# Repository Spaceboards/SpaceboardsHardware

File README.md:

# Spaceboards Hardware

### Status Key

❌  Unfinished

⚠️ Untested

✔️ Tested and functional 

### Designs
| Name     | Status | Contributors | 
|----------|--------|--------------|
|  2% Milk |  ✔️    | [PyroL](https://github.com/PyrooL), [Soft_Sama](https://www.thingiverse.com/soft_sama) |
|  Akimbo  |   ⚠️   |              |
|  LongBoi |   ❌   |              |
|Pancake v1|  ✔️  | [MKUltra Corp](https://kbd.news/vendors/MKUltra-129.html)  | 
|Pancake v2|  ✔️  | [MKUltra Corp](https://kbd.news/vendors/MKUltra-129.html)  |
|  Waffle  |  ⚠️    |              |
|  XLant   |  ⚠️    |              |

All of these files are shared under `CERN Open Hardware Licence Version 2 - Weakly Reciprocal`
Link this repository if you are selling any of these designs, These files are shared as is without any implied warranty or promise of being functional.

Visit our website at [https://spaceboards.github.io/](https://spaceboards.github.io/)

## Star History

<a href="https://www.star-history.com/?repos=Spaceboards%2FSpaceboardsHardware&type=date&legend=top-left">
 <picture>
   <source media="(prefers-color-scheme: dark)" srcset="https://api.star-history.com/chart?repos=Spaceboards/SpaceboardsHardware&type=date&theme=dark&legend=top-left" />
   <source media="(prefers-color-scheme: light)" srcset="https://api.star-history.com/chart?repos=Spaceboards/SpaceboardsHardware&type=date&legend=top-left" />
   
 </picture>
</a>

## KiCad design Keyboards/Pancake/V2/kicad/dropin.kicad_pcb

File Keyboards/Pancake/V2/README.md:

# Pancake v2

4x12 Choc v1 Ortho ultra low profile keyboard

- OLED screen

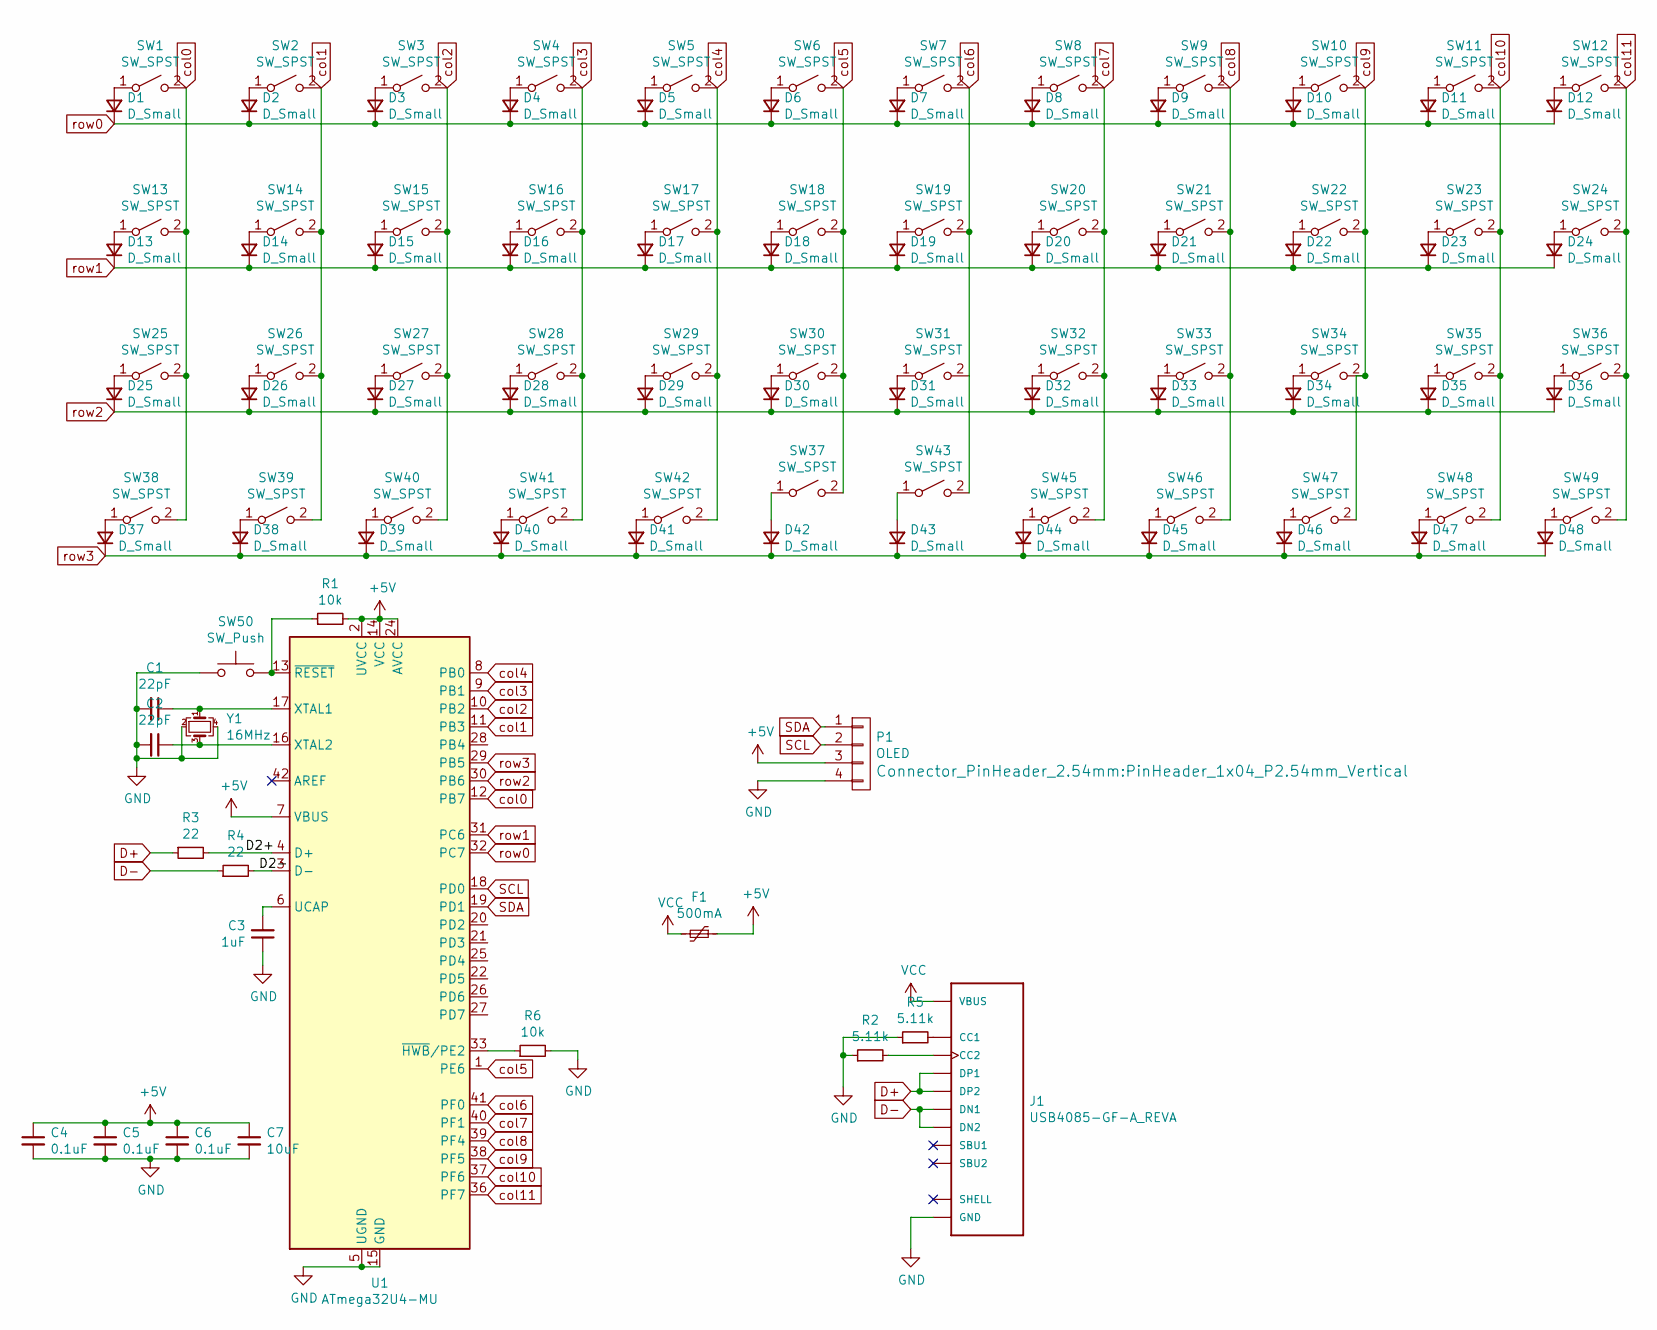
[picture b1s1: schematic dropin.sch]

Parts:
C1, C2: 22pF; C_0805_2012Metric
C3: 1uF; C_0805_2012Metric
C4, C5, C6: 0.1uF; C_0805_2012Metric
C7: 10uF; C_0805_2012Metric
D1, D2, D3, D4, D5, D6, D7, D8, D9, D10, D11, D12, D13, D14, D15, D16, D17, D18, D19, D20, D21, D22, D23, D24, D25, D26, D27, D28, D29, D30, D31, D32, D33, D34, D35, D36, D37, D38, D39, D40, D41, D42, D43, D44, D45, D46, D47, D48: D_Small; D_SOD123
F1: 500mA; Fuse_1206_3216Metric
J1: USB4085-GF-A_REVA; GCT_USB4085-GF-A_REVA
P1: OLED; PinHeader_1x04_P2.54mm_Vertical
R1, R6: 10k; R_0805_2012Metric
R2, R5: 5.11k; R_0805_2012Metric
R3, R4: 22; R_0805_2012Metric
SW1, SW2, SW3, SW4, SW5, SW6, SW7, SW8, SW9, SW10, SW11, SW12, SW13, SW14, SW15, SW16, SW17, SW18, SW19, SW20, SW21, SW22, SW23, SW24, SW25, SW26, SW27, SW28, SW29, SW30, SW31, SW32, SW33, SW34, SW35, SW36, SW38, SW39, SW40, SW41, SW42, SW45, SW46, SW47, SW48, SW49: SW_SPST; Kailh-PG1350-1u-NoLED
SW37, SW43: SW_SPST; Kailh-PG1350-1.5u-NoLED
SW50: SW_Push; SW_SPST_SKQG_WithoutStem
U1: ATmega32U4-MU; QFN-44-1EP_7x7mm_P0.5mm_EP5.2x5.2mm
Y1: 16MHz; Crystal_SMD_3225-4Pin_3.2x2.5mm

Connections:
+5V: C4.1, C5.1, C6.1, C7.1, F1.1, P1.3, R1.2, U1.2 (UVCC), U1.7 (VBUS), U1.14 (VCC), U1.24 (AVCC), U1.34 (VCC), U1.44 (AVCC)
/D2+: R3.2, U1.4 (D+)
/D2-: R4.2, U1.3 (D-)
D+: J1.A6 (DP1), J1.B6 (DP2), R3.1
D-: J1.A7 (DN1), J1.B7 (DN2), R4.1
GND: C1.2, C2.2, C3.1, C4.2, C5.2, C6.2, C7.2, J1.A1 (GND), J1.A12 (GND), J1.B1 (GND), J1.B12 (GND), P1.4, R2.1, R5.1, R6.2, SW50.1, U1.5 (UGND), U1.15 (GND), U1.23 (GND), U1.35 (GND), U1.43 (GND), U1.45 (GND), Y1.2, Y1.4
unnamed: C1.1, U1.17 (XTAL1), Y1.1
unnamed: C2.1, U1.16 (XTAL2), Y1.3
unnamed: C3.2, U1.6 (UCAP)
unnamed: D1.2 (A), SW1.1 (A)
unnamed: D2.2 (A), SW2.1 (A)
unnamed: D3.2 (A), SW3.1 (A)
unnamed: D4.2 (A), SW4.1 (A)
unnamed: D5.2 (A), SW5.1 (A)
unnamed: D6.2 (A), SW6.1 (A)
unnamed: D7.2 (A), SW7.1 (A)
unnamed: D8.2 (A), SW8.1 (A)
unnamed: D9.2 (A), SW9.1 (A)
unnamed: D10.2 (A), SW10.1 (A)
unnamed: D11.2 (A), SW11.1 (A)
unnamed: D12.2 (A), SW12.1 (A)
unnamed: D13.2 (A), SW13.1 (A)
unnamed: D14.2 (A), SW14.1 (A)
unnamed: D15.2 (A), SW15.1 (A)
unnamed: D16.2 (A), SW16.1 (A)
unnamed: D17.2 (A), SW17.1 (A)
unnamed: D18.2 (A), SW18.1 (A)
unnamed: D19.2 (A), SW19.1 (A)
unnamed: D20.2 (A), SW20.1 (A)
unnamed: D21.2 (A), SW21.1 (A)
unnamed: D22.2 (A), SW22.1 (A)
unnamed: D23.2 (A), SW23.1 (A)
unnamed: D24.2 (A), SW24.1 (A)
unnamed: D25.2 (A), SW25.1 (A)
unnamed: D26.2 (A), SW26.1 (A)
unnamed: D27.2 (A), SW27.1 (A)
unnamed: D28.2 (A), SW28.1 (A)
unnamed: D29.2 (A), SW29.1 (A)
unnamed: D30.2 (A), SW30.1 (A)
unnamed: D31.2 (A), SW31.1 (A)
unnamed: D32.2 (A), SW32.1 (A)
unnamed: D33.2 (A), SW33.1 (A)
unnamed: D34.2 (A), SW34.1 (A)
unnamed: D35.2 (A), SW35.1 (A)
unnamed: D36.2 (A), SW36.1 (A)
unnamed: D37.2 (A), SW38.1 (A)
unnamed: D38.2 (A), SW39.1 (A)
unnamed: D39.2 (A), SW40.1 (A)
unnamed: D40.2 (A), SW41.1 (A)
unnamed: D41.2 (A), SW42.1 (A)
unnamed: D42.2 (A), SW37.1 (A)
unnamed: D43.2 (A), SW43.1 (A)
unnamed: D44.2 (A), SW45.1 (A)
unnamed: D45.2 (A), SW46.1 (A)
unnamed: D46.2 (A), SW47.1 (A)
unnamed: D47.2 (A), SW48.1 (A)
unnamed: D48.2 (A), SW49.1 (A)
unnamed: J1.A5 (CC1), R5.2
unnamed: J1.B5 (CC2), R2.2
unnamed: J1.P1 (SHELL), J1.P2 (SHELL), J1.P3 (SHELL), J1.P4 (SHELL)
unnamed: R1.1, SW50.2, U1.13 (~RESET)
unnamed: R6.1, U1.33 (~HWB~/PE2)
SCL: P1.2, U1.18 (PD0)
SDA: P1.1, U1.19 (PD1)
VCC: F1.2, J1.A4 (VBUS), J1.A9 (VBUS), J1.B4 (VBUS), J1.B9 (VBUS)
col0: SW1.2 (B), SW13.2 (B), SW25.2 (B), SW38.2 (B), U1.12 (PB7)
col1: SW2.2 (B), SW14.2 (B), SW26.2 (B), SW39.2 (B), U1.11 (PB3)
col2: SW3.2 (B), SW15.2 (B), SW27.2 (B), SW40.2 (B), U1.10 (PB2)
col3: SW4.2 (B), SW16.2 (B), SW28.2 (B), SW41.2 (B), U1.9 (PB1)
col4: SW5.2 (B), SW17.2 (B), SW29.2 (B), SW42.2 (B), U1.8 (PB0)
col5: SW6.2 (B), SW18.2 (B), SW30.2 (B), SW37.2 (B), U1.1 (PE6)
col6: SW7.2 (B), SW19.2 (B), SW31.2 (B), SW43.2 (B), U1.41 (PF0)
col7: SW8.2 (B), SW20.2 (B), SW32.2 (B), SW45.2 (B), U1.40 (PF1)
col8: SW9.2 (B), SW21.2 (B), SW33.2 (B), SW46.2 (B), U1.39 (PF4)
col9: SW10.2 (B), SW22.2 (B), SW34.2 (B), SW47.2 (B), U1.38 (PF5)
col10: SW11.2 (B), SW23.2 (B), SW35.2 (B), SW48.2 (B), U1.37 (PF6)
col11: SW12.2 (B), SW24.2 (B), SW36.2 (B), SW49.2 (B), U1.36 (PF7)
row0: D1.1 (K), D2.1 (K), D3.1 (K), D4.1 (K), D5.1 (K), D6.1 (K), D7.1 (K), D8.1 (K), D9.1 (K), D10.1 (K), D11.1 (K), D12.1 (K), U1.32 (PC7)
row1: D13.1 (K), D14.1 (K), D15.1 (K), D16.1 (K), D17.1 (K), D18.1 (K), D19.1 (K), D20.1 (K), D21.1 (K), D22.1 (K), D23.1 (K), D24.1 (K), U1.31 (PC6)
row2: D25.1 (K), D26.1 (K), D27.1 (K), D28.1 (K), D29.1 (K), D30.1 (K), D31.1 (K), D32.1 (K), D33.1 (K), D34.1 (K), D35.1 (K), D36.1 (K), U1.30 (PB6)
row3: D37.1 (K), D38.1 (K), D39.1 (K), D40.1 (K), D41.1 (K), D42.1 (K), D43.1 (K), D44.1 (K), D45.1 (K), D46.1 (K), D47.1 (K), D48.1 (K), U1.29 (PB5)

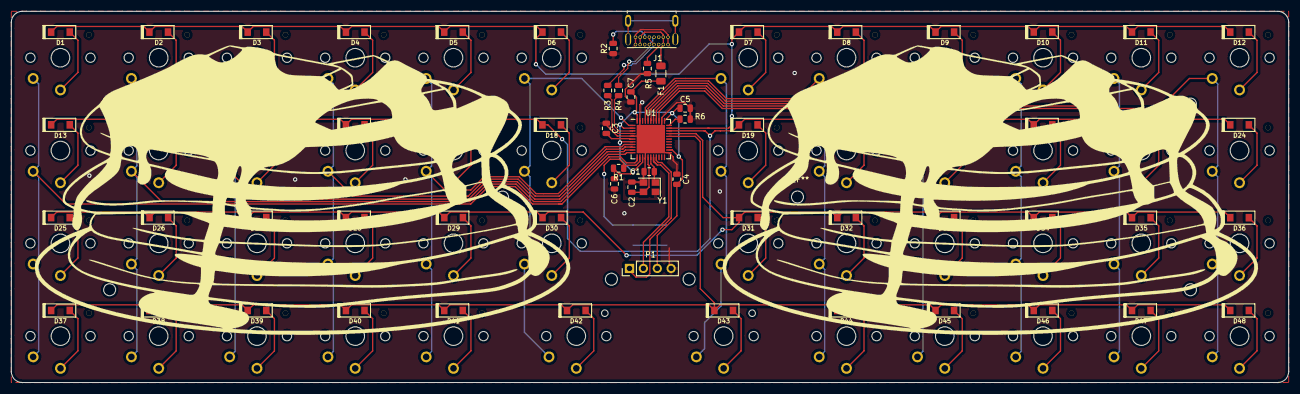
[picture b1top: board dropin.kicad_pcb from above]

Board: 2 copper layers, 234.0 x 68.0 mm, 115 parts (1 on the bottom side), 81 nets.

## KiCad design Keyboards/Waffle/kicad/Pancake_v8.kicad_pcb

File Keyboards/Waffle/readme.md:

# Waffle
A Bluetooth 4x12 ortho keyboard that uses Choc switches and an [Adafruit Feather](https://www.adafruit.com/product/2829)
- PCB is currently untested order at your own risk
- There is currently no firmware in qmk for this board

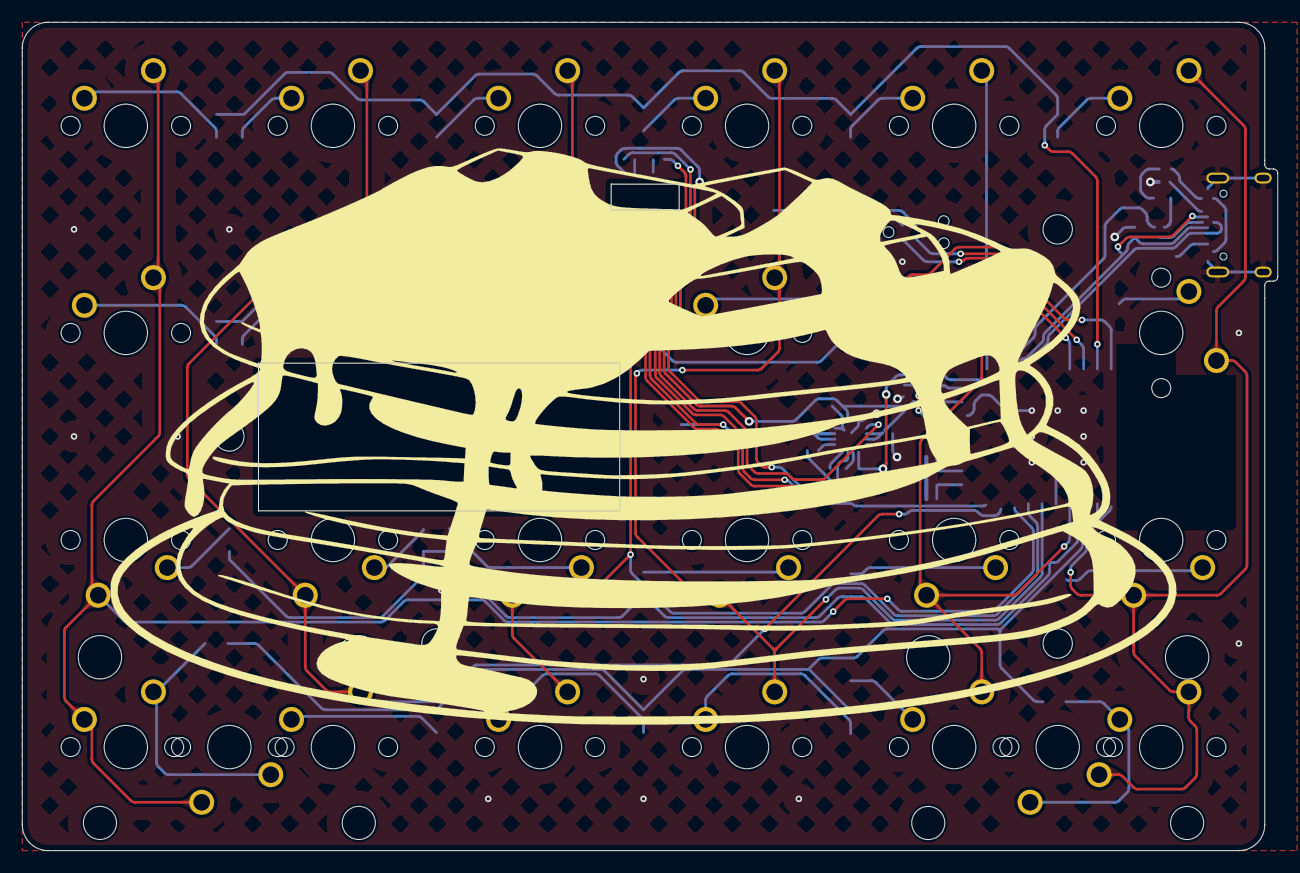
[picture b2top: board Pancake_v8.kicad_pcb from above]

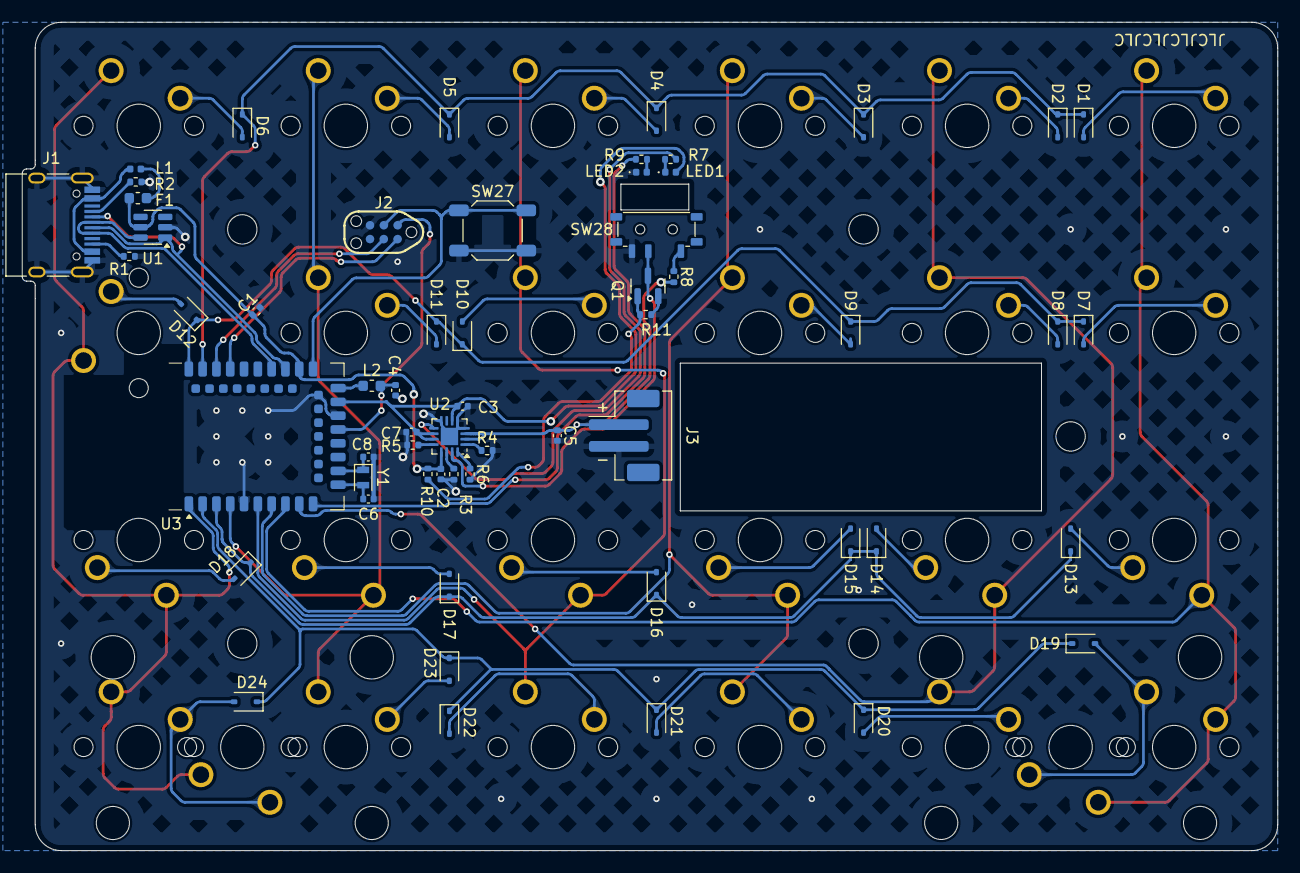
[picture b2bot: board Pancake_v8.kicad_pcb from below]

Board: 2 copper layers, 115.5 x 76.2 mm, 91 parts (58 on the bottom side), 62 nets.

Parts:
C1, C2, C3, C5, C7: 4u7; C_0402_1005Metric
C4: 1u; C_0402_1005Metric
C6, C8: 12p; C_0402_1005Metric
D1, D2, D3, D4, D5, D6, D7, D8, D9, D10, D11, D12, D13, D14, D15, D16, D17, D18, D19, D20, D21, D22, D23, D24: D_Small; D_SOD-323
F1: 750 mA; Fuse_0603_1608Metric
H1, H2, H3, H4, H5: MountingHole; MountingHole_2.7mm_M2.5
J1: HRO_TYPE-C-31-M-14; USB_C_Receptacle_HRO_TYPE-C-31-M-12
J2: TC2030_SWD; CON_TC2030_outlined
J3: Battery; JST_PH_B2B-PH-SM4-TB_1x02-1MP_P2.00mm_Vertical
L1: BLM15PX121SN1D; L_0402_1005Metric
L2: 10 uH; L_0603_1608Metric
LED1: Orange; LED_0402_1005Metric
LED2: Blue; LED_0402_1005Metric
Q1: 2N7002; SOT-23
R1, R2: 5k1; R_0402_1005Metric
R3: 47k; R_0402_1005Metric
R4, R7, R9, R11: 10k; R_0402_1005Metric
R5: 1k5; R_0402_1005Metric
R6: 3k9; R_0402_1005Metric
R8: 100k; R_0402_1005Metric
R10: 100R; R_0402_1005Metric
S1, S2: MX_stab; STAB_MX_2u
SW1, SW2, SW3, SW4, SW5, SW6, SW7, SW8, SW9, SW10, SW11, SW12, SW13, SW14, SW15, SW16, SW17, SW18, SW19, SW20, SW21, SW22, SW23, SW24, SW25, SW26: SW_Push_45deg; SW_MX_1u
SW27: RST; SW_SPST_SKQG_WithStem
SW28: PWR; SW_MSK12C02-HB
U1: SRV05-4; SOT-23-6
U2: BQ24075; VQFN-16-1EP_3x3mm_P0.5mm_EP1.6x1.6mm
U3: nRF52840_E73-2G4M08S1C
Y1: 32.768 KHz; Crystal_SMD_2012-2Pin_2.0x1.2mm

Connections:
+5V: C1.1, C2.1, F1.1, R10.1, U1.5 (VP), U2.13 (IN), U3.27 (VBUS)
+BATT: C5.1, J3.1, R8.2, U2.2 (BAT), U2.3 (BAT)
+VSW: C3.1, C7.1, LED1.2 (A), U2.6 (EN1), U2.10 (OUT), U2.11 (OUT), U3.23 (VDDH)
/ILIM: R5.1, U2.12 (ILIM)
/TMR: R3.1, U2.14 (TMR)
BOOT: R9.1, U3.10 (P0.30/AIN6)
DCCH: L2.1, U3.25 (DCCH)
GND: C1.2, C2.2, C3.2, C4.2, C5.2, C6.2, C7.2, C8.2, J1.A1 (GND), J1.A12 (GND), J1.B1 (GND), J1.B12 (GND), J1.S1 (SHIELD), J2.5 (GND), J3.2, LED2.1 (K), Q1.2 (S), R1.1, R2.1, R3.2, R4.2, R5.2, R6.2, R11.2, SW27.2, SW28.3 (C), U1.2 (VN), U2.4 (~CE), U2.5 (EN2), U2.8 (VSS), U2.17 (VSS), U3.5 (GND), U3.21 (GND), U3.24 (GND)
unnamed: D1.2 (A), SW1.1
unnamed: D2.2 (A), SW2.1
unnamed: D3.2 (A), SW3.1
unnamed: D4.2 (A), SW4.1
unnamed: D5.2 (A), SW5.1
unnamed: D6.2 (A), SW6.1
unnamed: D7.2 (A), SW7.1
unnamed: D8.2 (A), SW8.1
unnamed: D9.2 (A), SW9.1
unnamed: D10.2 (A), SW10.1
unnamed: D11.2 (A), SW11.1
unnamed: D12.2 (A), SW12.1
unnamed: D13.2 (A), SW13.1
unnamed: D14.2 (A), SW14.1
unnamed: D15.2 (A), SW15.1
unnamed: D16.2 (A), SW16.1
unnamed: D17.2 (A), SW17.1
unnamed: D18.2 (A), SW18.1
unnamed: D19.2 (A), SW19.2, SW20.1
unnamed: D20.2 (A), SW21.1
unnamed: D21.2 (A), SW22.1
unnamed: D22.2 (A), SW23.1
unnamed: D23.2 (A), SW24.1
unnamed: D24.2 (A), SW25.2, SW26.1
unnamed: F1.2, L1.2
unnamed: J1.A5 (CC1), R2.2
unnamed: J1.B5 (CC2), R1.2
unnamed: LED1.1 (K), R7.2
unnamed: LED2.2 (A), R9.2
unnamed: Q1.1 (G), R10.2, R11.1
unnamed: R8.1, SW28.1 (A)
unnamed: R6.1, U2.16 (ISET)
unnamed: R4.1, U2.1 (TS)
unnamed: R7.1, U2.9 (~CHG)
unnamed: C6.1, U3.11 (P0.00/XL1), Y1.2
unnamed: C8.1, U3.13 (P0.01/XL2), Y1.1
RST: J2.3 (~RST), SW27.1, U3.26 (P0.18/~RESET)
SWDCLK: J2.4 (SWCLK), U3.39 (SWDCLK)
SWDIO: J2.2 (SWDIO), U3.37 (SWDIO)
SYSOFF: Q1.3 (D), SW28.2 (B), U2.15 (SYSOFF)
USB-D+: J1.A6 (D+), J1.B6 (D+), U1.6 (IO4), U3.31 (D+)
USB-D-: J1.A7 (D-), J1.B7 (D-), U1.1 (IO1), U3.29 (D-)
VBUS: J1.A4 (VBUS), J1.A9 (VBUS), J1.B4 (VBUS), J1.B9 (VBUS), L1.1
VDD: C4.1, J2.1 (VCC), L2.2, U3.19 (VDD)
c0: SW1.2, SW7.2, SW13.2, SW19.1, SW20.2, U3.8 (P0.29/AIN5)
c1: SW2.2, SW8.2, SW14.2, SW21.2, U3.9 (P0.31/AIN7)
c2: SW3.2, SW9.2, SW15.2, SW22.2, U3.7 (P0.02/AIN0)
c3: SW4.2, SW10.2, SW16.2, SW23.2, U3.6 (P1.13)
c4: SW5.2, SW11.2, SW17.2, SW24.2, U3.4 (P0.28/AIN4)
c5: SW6.2, SW12.2, SW18.2, SW25.1, SW26.2, U3.1 (P1.11)
r0: D1.1 (K), D2.1 (K), D3.1 (K), D4.1 (K), D5.1 (K), D6.1 (K), U3.41 (P0.09/NFC1)
r1: D7.1 (K), D8.1 (K), D9.1 (K), D10.1 (K), D11.1 (K), D12.1 (K), U3.43 (P0.10/NFC2)
r2: D13.1 (K), D14.1 (K), D15.1 (K), D16.1 (K), D17.1 (K), D18.1 (K), U3.3 (P0.03/AIN1)
r3: D19.1 (K), D20.1 (K), D21.1 (K), D22.1 (K), D23.1 (K), D24.1 (K), U3.2 (P1.10)

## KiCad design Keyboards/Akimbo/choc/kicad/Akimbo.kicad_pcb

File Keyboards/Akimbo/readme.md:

# Akimbo

You only have 10 fingers why would you need more than 10 keys

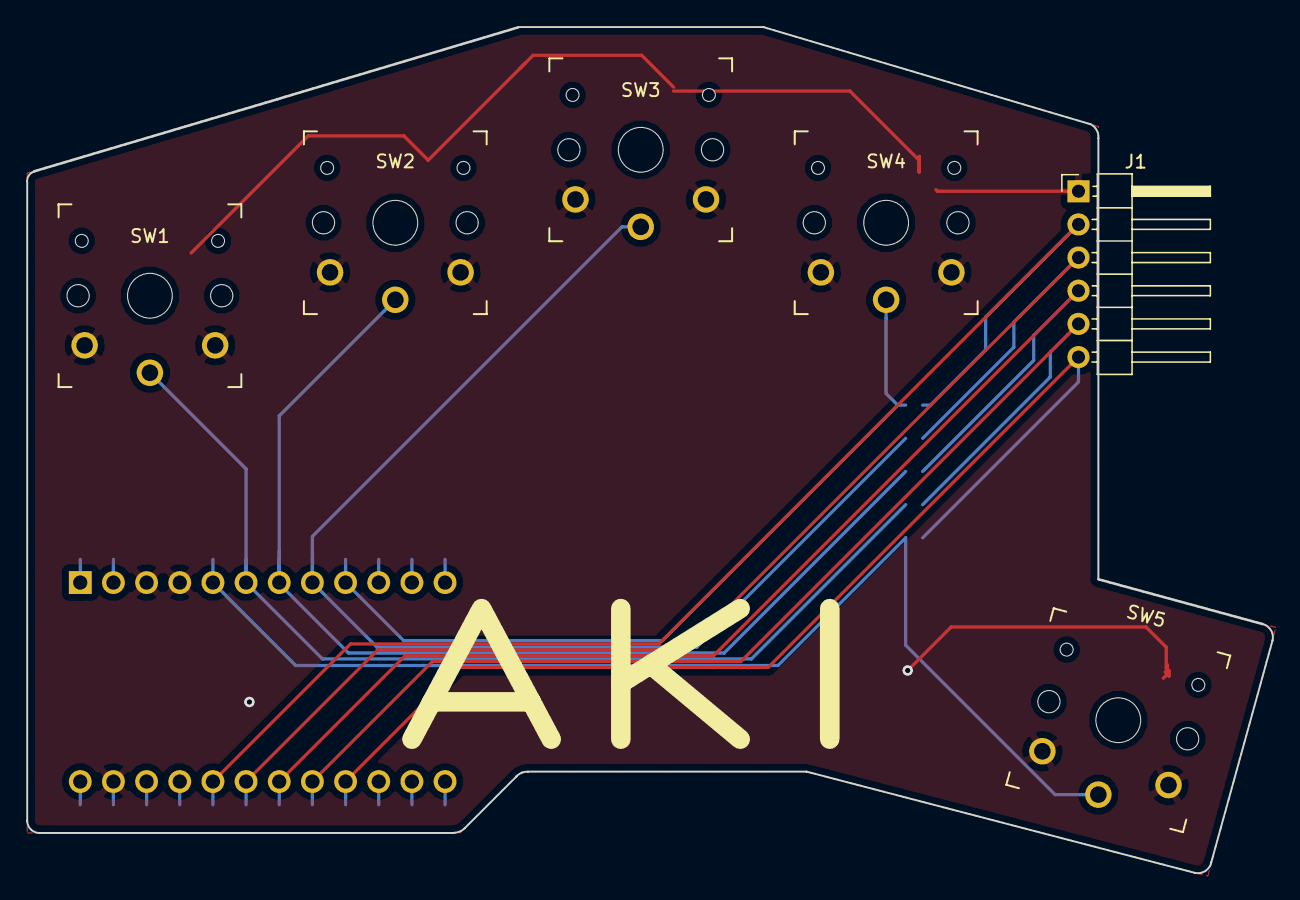
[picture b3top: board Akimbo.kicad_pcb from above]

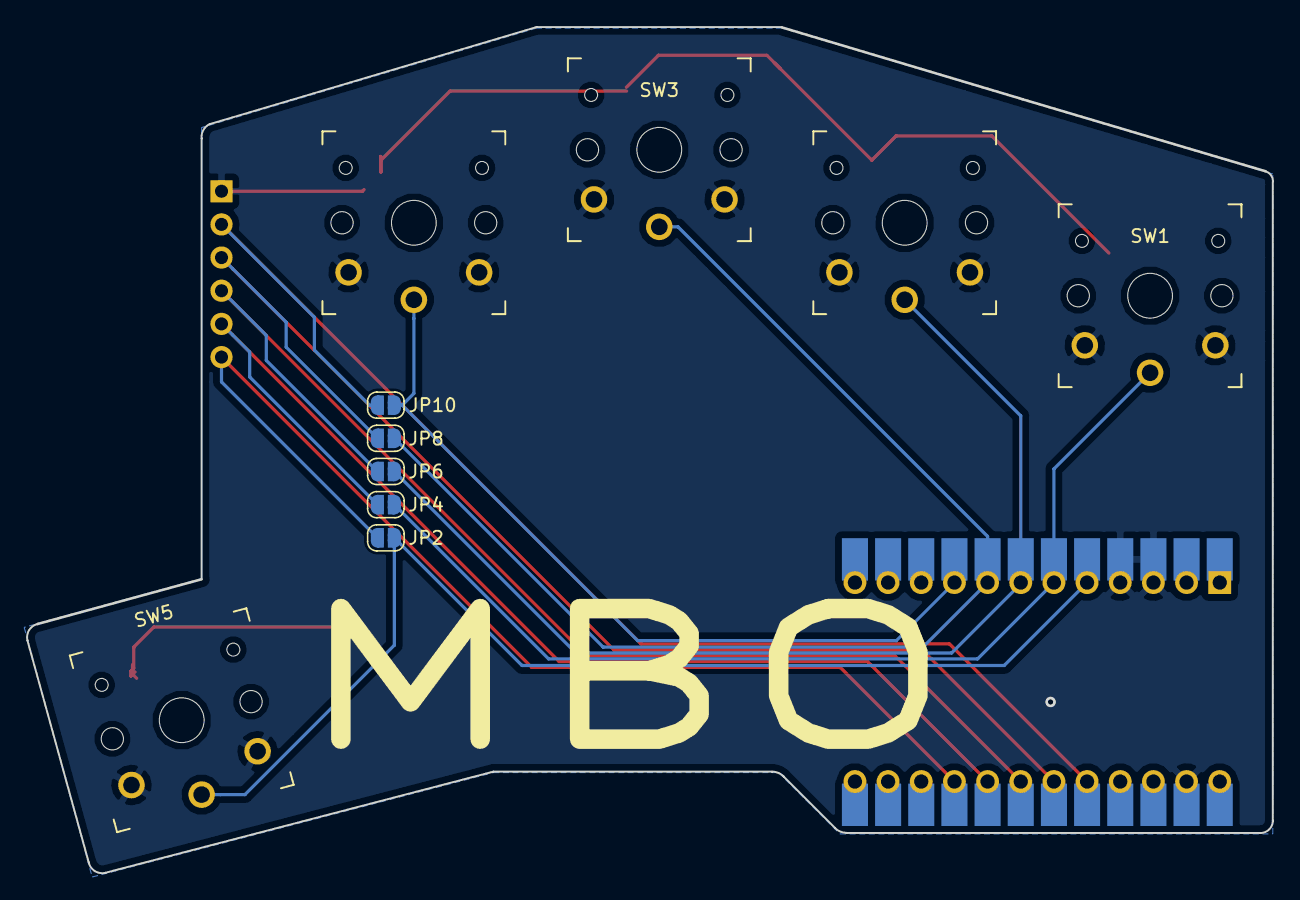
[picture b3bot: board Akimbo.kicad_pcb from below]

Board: 2 copper layers, 95.4 x 64.8 mm, 12 parts (6 on the bottom side), 11 nets.

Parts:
J1: Conn_01x06_Male; PinHeader_1x06_P2.54mm_Horizontal
JP2, JP4, JP6, JP8, JP10: Jumper_NO_Small; SolderJumper-2_P1.3mm_Open_RoundedPad1.0x1.5mm
SW1, SW2, SW3, SW4, SW5: SW_Push; SW_PG1350_reversible
U1: ProMicro; Elite-C-v3_with_holes_no_xtra

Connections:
/SW1: JP2.1, SW5.1, U1.5
/SW2: JP4.1, SW1.1, U1.6
/SW3: JP6.1, SW2.1, U1.7
/SW4: JP8.1, SW3.1, U1.8
/SW5: JP10.1, SW4.1, U1.9
/SW6: J1.6, JP2.2, U1.16
/SW7: J1.5, JP4.2, U1.17
/SW8: J1.4, JP6.2, U1.18
/SW9: J1.3, JP8.2, U1.19
/SW10: J1.2, JP10.2, U1.20
GND: J1.1, SW1.2, SW2.2, SW3.2, SW4.2, SW5.2, U1.3, U1.4, U1.23

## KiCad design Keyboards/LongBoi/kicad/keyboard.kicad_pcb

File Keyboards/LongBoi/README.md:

# Long Boi

a 3x21 ortho board

- Currently Untested
- No Case for this keyboard currently
- No firmware in QMK for this keyboard

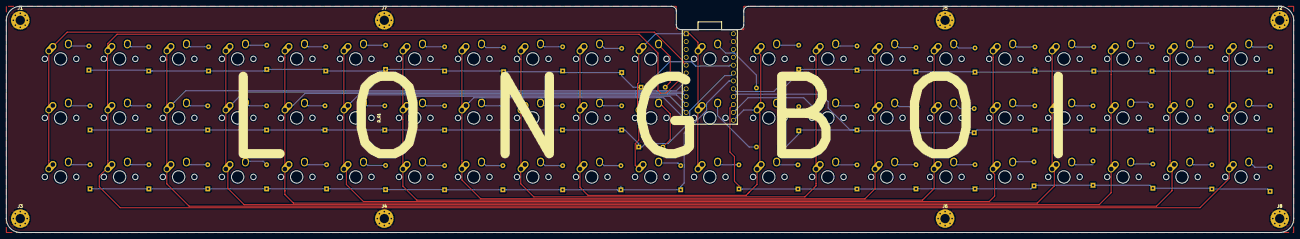
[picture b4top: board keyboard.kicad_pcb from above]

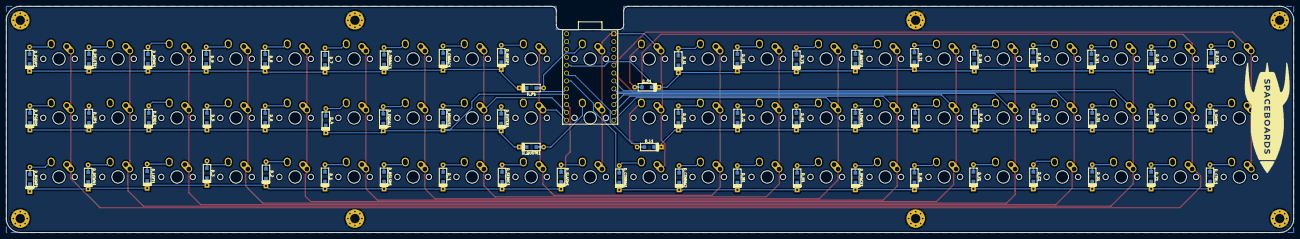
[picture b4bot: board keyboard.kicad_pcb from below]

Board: 2 copper layers, 415.5 x 73.0 mm, 135 parts (63 on the bottom side), 81 nets.

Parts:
D_1, D_2, D_3, D_4, D_5, D_6, D_7, D_8, D_9: D; D_SOD123_axial
D_A1: D; D_SOD123_axial
D_B1: D; D_SOD123_axial
D_BKSP1: D; D_SOD123_axial
D_BSLSH1: D; D_SOD123_axial
D_C1: D; D_SOD123_axial
D_CBRAC1: D; D_SOD123_axial
D_COMMA1, D_COMMA2: D; D_SOD123_axial
D_CTRL1: D; D_SOD123_axial
D_D1: D; D_SOD123_axial
D_DELETE1: D; D_SOD123_axial
D_DOWN1: D; D_SOD123_axial
D_E1: D; D_SOD123_axial
D_END1: D; D_SOD123_axial
D_ENTER1: D; D_SOD123_axial
D_EQUAL1: D; D_SOD123_axial
D_ESC1: D; D_SOD123_axial
D_F1: D; D_SOD123_axial
D_G1: D; D_SOD123_axial
D_H1: D; D_SOD123_axial
D_HOME1: D; D_SOD123_axial
D_I1: D; D_SOD123_axial
D_J1: D; D_SOD123_axial
D_K1: D; D_SOD123_axial
D_L1: D; D_SOD123_axial
D_LEFT1: D; D_SOD123_axial
D_LOWER1: D; D_SOD123_axial
D_M1: D; D_SOD123_axial
D_MINUS1: D; D_SOD123_axial
D_N1: D; D_SOD123_axial
D_O1: D; D_SOD123_axial
D_OBRAC1: D; D_SOD123_axial
D_P1: D; D_SOD123_axial
D_PGDN1: D; D_SOD123_axial
D_PGUP1: D; D_SOD123_axial
D_Q1: D; D_SOD123_axial
D_QUOTE1: D; D_SOD123_axial
D_R1: D; D_SOD123_axial
D_RAISE1: D; D_SOD123_axial
D_RIGHT1: D; D_SOD123_axial
D_S1: D; D_SOD123_axial
D_SEMIC1: D; D_SOD123_axial
D_SHIFT1: D; D_SOD123_axial
D_SLASH1: D; D_SOD123_axial
D_SPACE1: D; D_SOD123_axial
D_T1: D; D_SOD123_axial
D_U1: D; D_SOD123_axial
D_UP1: D; D_SOD123_axial
D_V1: D; D_SOD123_axial
D_W1: D; D_SOD123_axial
D_X1: D; D_SOD123_axial
D_Y1: D; D_SOD123_axial
D_Z1: D; D_SOD123_axial
D_`1: D; D_SOD123_axial
J1, J2, J3, J4, J5, J6, J7, J8: Conn_01x01_Female; MountingHole_3mm_Pad_Via
K_1, K_2, K_3, K_4, K_5, K_6, K_7, K_8, K_9: KEYSW; MX-1U-NoLED
K_A1: KEYSW; MX-1U-NoLED
K_B1: KEYSW; MX-1U-NoLED
K_BKSP1: KEYSW; MX-1U-NoLED
K_BSLSH1: KEYSW; MX-1U-NoLED
K_C1: KEYSW; MX-1U-NoLED
K_CBRAC1: KEYSW; MX-1U-NoLED
K_COMMA1, K_COMMA2: KEYSW; MX-1U-NoLED
K_CTRL1: KEYSW; MX-1U-NoLED
K_D1: KEYSW; MX-1U-NoLED
K_DELETE1: KEYSW; MX-1U-NoLED
K_DOWN1: KEYSW; MX-1U-NoLED
K_E1: KEYSW; MX-1U-NoLED
K_END1: KEYSW; MX-1U-NoLED
K_ENTER1: KEYSW; MX-1U-NoLED
K_EQUAL1: KEYSW; MX-1U-NoLED
K_ESC1: KEYSW; MX-1U-NoLED
K_F1: KEYSW; MX-1U-NoLED
K_G1: KEYSW; MX-1U-NoLED
K_H1: KEYSW; MX-1U-NoLED
K_HOME1: KEYSW; MX-1U-NoLED
K_I1: KEYSW; MX-1U-NoLED
K_J1: KEYSW; MX-1U-NoLED
K_K1: KEYSW; MX-1U-NoLED
K_L1: KEYSW; MX-1U-NoLED
K_LEFT1: KEYSW; MX-1U-NoLED
K_LOWER1: KEYSW; MX-1U-NoLED
K_M1: KEYSW; MX-1U-NoLED
K_MINUS1: KEYSW; MX-1U-NoLED
K_N1: KEYSW; MX-1U-NoLED
K_O1: KEYSW; MX-1U-NoLED
K_OBRAC1: KEYSW; MX-1U-NoLED
K_P1: KEYSW; MX-1U-NoLED
K_PGDN1: KEYSW; MX-1U-NoLED
K_PGUP1: KEYSW; MX-1U-NoLED
K_Q1: KEYSW; MX-1U-NoLED
K_QUOTE1: KEYSW; MX-1U-NoLED
K_R1: KEYSW; MX-1U-NoLED
K_RAISE1: KEYSW; MX-1U-NoLED
K_RIGHT1: KEYSW; MX-1U-NoLED
K_S1: KEYSW; MX-1U-NoLED
K_SEMIC1: KEYSW; MX-1U-NoLED
K_SHIFT1: KEYSW; MX-1U-NoLED
K_SLASH1: KEYSW; MX-1U-NoLED
K_SPACE1: KEYSW; MX-1U-NoLED
K_T1: KEYSW; MX-1U-NoLED
K_U1: KEYSW; MX-1U-NoLED
K_UP1: KEYSW; MX-1U-NoLED
K_V1: KEYSW; MX-1U-NoLED
K_W1: KEYSW; MX-1U-NoLED
K_X1: KEYSW; MX-1U-NoLED
K_Y1: KEYSW; MX-1U-NoLED
K_Z1: KEYSW; MX-1U-NoLED
K_`1: KEYSW; MX-1U-NoLED
U1: ProMicro

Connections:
GND: J1.1, J2.1, J3.1, J4.1, J5.1, J6.1, J7.1, J8.1, U1.23
unnamed: D_1.2, K_1.2
unnamed: D_2.2, K_2.2
unnamed: D_3.2, K_3.2
unnamed: D_4.2, K_4.2
unnamed: D_5.2, K_5.2
unnamed: D_6.2, K_6.2
unnamed: D_7.2, K_7.2
unnamed: D_8.2, K_8.2
unnamed: D_9.2, K_9.2
unnamed: D_A1.2, K_A1.2
unnamed: D_B1.2, K_B1.2
unnamed: D_BKSP1.2, K_BKSP1.2
unnamed: D_BSLSH1.2, K_BSLSH1.2
unnamed: D_C1.2, K_C1.2
unnamed: D_CBRAC1.2, K_CBRAC1.2
unnamed: D_COMMA1.2, K_COMMA1.2
unnamed: D_COMMA2.2, K_COMMA2.2
unnamed: D_CTRL1.2, K_CTRL1.2
unnamed: D_D1.2, K_D1.2
unnamed: D_DELETE1.2, K_DELETE1.2
unnamed: D_DOWN1.2, K_DOWN1.2
unnamed: D_E1.2, K_E1.2
unnamed: D_END1.2, K_END1.2
unnamed: D_ENTER1.2, K_ENTER1.2
unnamed: D_EQUAL1.2, K_EQUAL1.2
unnamed: D_ESC1.2, K_ESC1.2
unnamed: D_F1.2, K_F1.2
unnamed: D_G1.2, K_G1.2
unnamed: D_H1.2, K_H1.2
unnamed: D_HOME1.2, K_HOME1.2
unnamed: D_I1.2, K_I1.2
unnamed: D_J1.2, K_J1.2
unnamed: D_K1.2, K_K1.2
unnamed: D_L1.2, K_L1.2
unnamed: D_LEFT1.2, K_LEFT1.2
unnamed: D_LOWER1.2, K_LOWER1.2
unnamed: D_M1.2, K_M1.2
unnamed: D_MINUS1.2, K_MINUS1.2
unnamed: D_N1.2, K_N1.2
unnamed: D_O1.2, K_O1.2
unnamed: D_OBRAC1.2, K_OBRAC1.2
unnamed: D_P1.2, K_P1.2
unnamed: D_PGDN1.2, K_PGDN1.2
unnamed: D_PGUP1.2, K_PGUP1.2
unnamed: D_Q1.2, K_Q1.2
unnamed: D_QUOTE1.2, K_QUOTE1.2
unnamed: D_R1.2, K_R1.2
unnamed: D_RAISE1.2, K_RAISE1.2
unnamed: D_RIGHT1.2, K_RIGHT1.2
unnamed: D_S1.2, K_S1.2
unnamed: D_SEMIC1.2, K_SEMIC1.2
unnamed: D_SHIFT1.2, K_SHIFT1.2
unnamed: D_SLASH1.2, K_SLASH1.2
unnamed: D_SPACE1.2, K_SPACE1.2
unnamed: D_T1.2, K_T1.2
unnamed: D_U1.2, K_U1.2
unnamed: D_UP1.2, K_UP1.2
unnamed: D_V1.2, K_V1.2
unnamed: D_W1.2, K_W1.2
unnamed: D_X1.2, K_X1.2
unnamed: D_Y1.2, K_Y1.2
unnamed: D_Z1.2, K_Z1.2
unnamed: D_`1.2, K_`1.2
col0: K_CTRL1.1, K_ESC1.1, K_SHIFT1.1, U1.5
col1: K_A1.1, K_PGDN1.1, K_PGUP1.1, K_Q1.1, K_RIGHT1.1, K_Z1.1, U1.6
col2: K_DELETE1.1, K_DOWN1.1, K_S1.1, K_UP1.1, K_W1.1, K_X1.1, U1.7
col3: K_C1.1, K_D1.1, K_E1.1, K_END1.1, K_HOME1.1, K_LEFT1.1, U1.8
col4: K_3.1, K_5.1, K_9.1, K_F1.1, K_R1.1, K_V1.1, U1.9
col5: K_2.1, K_6.1, K_8.1, K_B1.1, K_G1.1, K_T1.1, U1.10
col6: K_1.1, K_4.1, K_7.1, K_LOWER1.1, K_RAISE1.1, K_SPACE1.1, U1.11
col7: K_BSLSH1.1, K_EQUAL1.1, K_H1.1, K_N1.1, K_OBRAC1.1, K_Y1.1, U1.12
col8: K_CBRAC1.1, K_J1.1, K_M1.1, K_MINUS1.1, K_U1.1, K_`1.1, U1.14
col9: K_BKSP1.1, K_COMMA2.1, K_ENTER1.1, K_I1.1, K_K1.1, K_SEMIC1.1, U1.13
col10: K_COMMA1.1, K_L1.1, K_O1.1, K_P1.1, K_QUOTE1.1, K_SLASH1.1, U1.1
row0: D_E1.1, D_ESC1.1, D_I1.1, D_O1.1, D_Q1.1, D_R1.1, D_RAISE1.1, D_T1.1, D_U1.1, D_W1.1, D_Y1.1, U1.20
row1: D_A1.1, D_D1.1, D_F1.1, D_G1.1, D_H1.1, D_J1.1, D_K1.1, D_L1.1, D_LOWER1.1, D_S1.1, D_SHIFT1.1, U1.19
row2: D_B1.1, D_C1.1, D_COMMA1.1, D_COMMA2.1, D_CTRL1.1, D_M1.1, D_N1.1, D_SPACE1.1, D_V1.1, D_X1.1, D_Z1.1, U1.18
row3: D_7.1, D_8.1, D_9.1, D_BKSP1.1, D_CBRAC1.1, D_DELETE1.1, D_HOME1.1, D_OBRAC1.1, D_P1.1, D_PGUP1.1, U1.17
row4: D_4.1, D_5.1, D_6.1, D_END1.1, D_ENTER1.1, D_EQUAL1.1, D_MINUS1.1, D_PGDN1.1, D_QUOTE1.1, D_UP1.1, U1.16
row5: D_1.1, D_2.1, D_3.1, D_BSLSH1.1, D_DOWN1.1, D_LEFT1.1, D_RIGHT1.1, D_SEMIC1.1, D_SLASH1.1, D_`1.1, U1.15

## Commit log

2019-05-16 make some folders public
2019-05-17 build guide ish
2019-05-20 reorganize
2019-05-23 add BAO
2019-05-26 Update Pancake
2019-05-31 Organize based on Progress
2019-05-31 add a couple of readme
2019-06-19 undo organize
2019-08-05 Open the flood gates
2019-08-06 label fix
2019-08-10 Create Random
2019-08-10 Rename Random/readme.md to etc/readme.md
2019-08-10 Rename etc/readme.md to random/readme.md
2019-12-16 Akimbo MX v2
    Fixed faulty footprint
2020-03-12 add XLant
2020-03-12 add screw holes to XLant
2020-03-15 what even is 19.05
2020-03-18 Update issue templates
2020-05-07 Update XLant
2020-09-06 Update license
2020-09-06 Remove all files that do not fit the license
2021-01-28 Update readme.md with correct link to build guide.
    The link to the build guide is 404'd. I visited https://spaceboards.xyz/hardware to get the correct link.
2022-10-25 Websites are expensive
2024-07-20 Add Pancake
2025-01-13 Convert to kicad folders
2025-01-13 Convert to folers
2025-01-14 Update waffle proto
2025-05-05 Update pancake v2
2025-05-05 Update funding
2026-04-12 Add Star History
